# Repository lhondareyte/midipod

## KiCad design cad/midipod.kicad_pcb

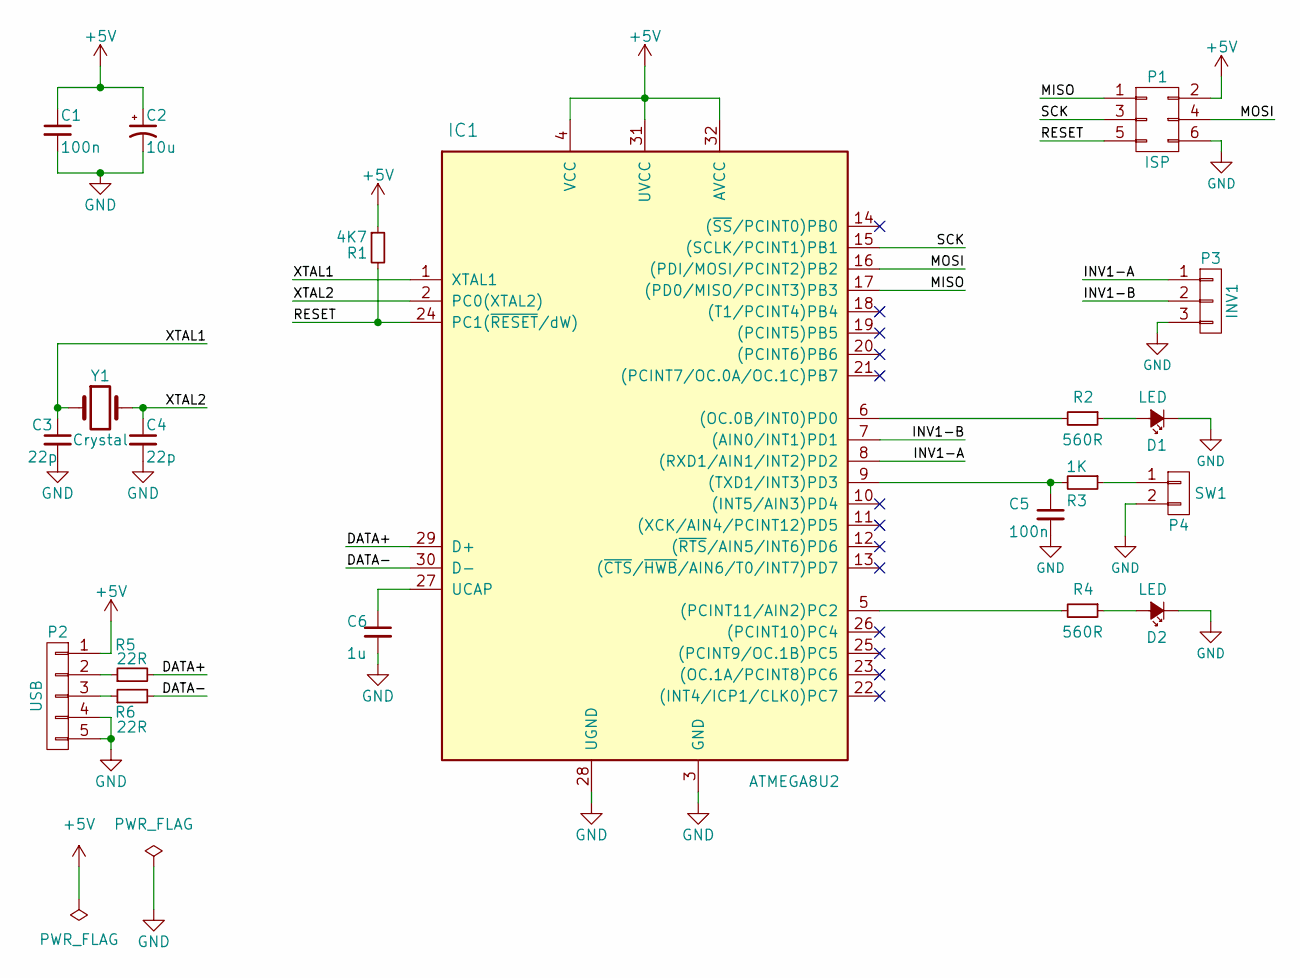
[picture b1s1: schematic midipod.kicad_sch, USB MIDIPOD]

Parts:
C1, C5: 100n; C_1206_HandSoldering
C2: 10u; C_Radial_D5_L11_P2.5
C3, C4: 22p; C_1206_HandSoldering
C6: 1u; C_1206_HandSoldering
D1, D2: LED; LED_D3.0mm_Horizontal_O1.27mm_Z2.0mm_Clear
IC1: ATMEGA8U2; TQFP-32_7x7mm_Pitch0.8mm
P1: ISP; Pin_Header_Straight_2x03
P2: USB; USB_B
P3: INV1; Pin_Header_Angled_1x03
P4: SW1; Pin_Header_Angled_1x02
R1: 4K7; R_1206_HandSoldering
R2, R4: 560R; R_1206_HandSoldering
R3: 1K; R_1206_HandSoldering
R5, R6: 22R; R_1206_HandSoldering
Y1: Crystal; Crystal_HC49-U_Vertical

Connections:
+5V: C1.1, C2.1, IC1.4 (VCC), IC1.31 (UVCC), IC1.32 (AVCC), P1.2, P2.1, R1.1
/DATA+: IC1.29 (D+), R5.2
/DATA-: IC1.30 (D-), R6.2
/INV1-A: IC1.8 ((RXD1/AIN1/INT2)PD2), P3.1
/INV1-B: IC1.7 ((AIN0/INT1)PD1), P3.2
/MISO: IC1.17 ((PD0/MISO/PCINT3)PB3), P1.1
/MOSI: IC1.16 ((PDI/MOSI/PCINT2)PB2), P1.4
/RESET: IC1.24 (PC1(~RESET/dW)), P1.5, R1.2
/SCK: IC1.15 ((SCLK/PCINT1)PB1), P1.3
/XTAL1: C3.1, IC1.1 (XTAL1), Y1.1
/XTAL2: C4.1, IC1.2 (PC0(XTAL2)), Y1.2
GND: C1.2, C2.2, C3.2, C4.2, C5.2, C6.2, D1.1 (K), D2.1 (K), IC1.3 (GND), IC1.28 (UGND), P1.6, P2.4, P2.5, P3.3, P4.2
unnamed: D1.2 (A), R2.1
unnamed: D2.2 (A), R4.1
unnamed: IC1.6 ((OC.0B/INT0)PD0), R2.2
unnamed: IC1.5 ((PCINT11/AIN2)PC2), R4.2
unnamed: C5.1, IC1.9 ((TXD1/INT3)PD3), R3.2
unnamed: C6.1, IC1.27 (UCAP)
unnamed: P2.2, R5.1
unnamed: P2.3, R6.1
unnamed: P4.1, R3.1

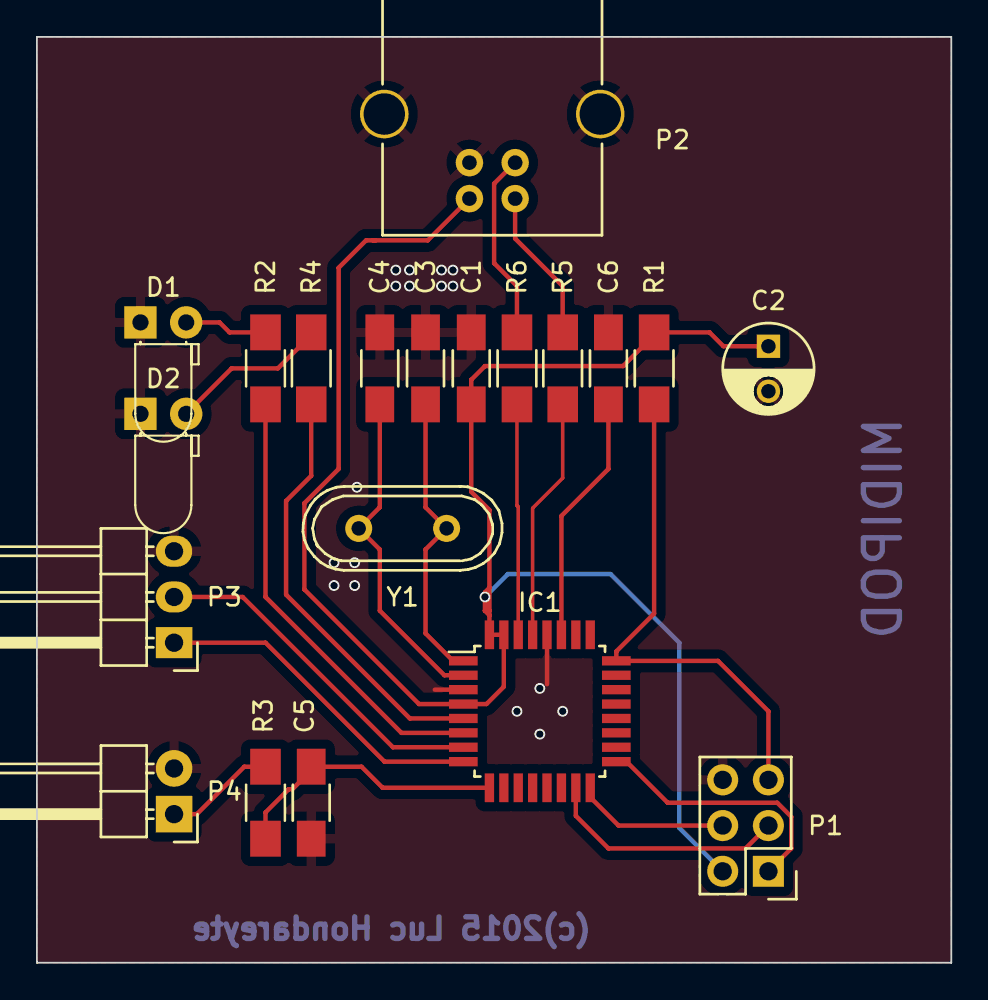
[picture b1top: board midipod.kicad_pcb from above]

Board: 2 copper layers, 50.8 x 51.4 mm, 20 parts (0 on the bottom side), 21 nets.

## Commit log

2014-03-11 Switch MIDI-USB. Premiere version fonctionnelle. Envoi d'un note unique non configurable.
2014-06-22 Switch d'offset OK. Modification PID et VID. Utilisattion des 2 Leds OK. Modification des IO conformement au schema V1.1.
2014-06-23 Ajout tempo dans la fonction SetupHardware -> Evite les erreurs USB_ERR_STALLED sous FreeBSD.
2014-08-03 Envoi d'un CC2 après le note-on. Modification de la fonction du switch 3 pos: il permet de modifier le niveau du CC2.
2018-11-19 Adding CAD and Medias files.
2018-11-19 Avoid F_CPU warning
2018-11-19 Turn on USB LED when connected
2018-11-19 Add .gitignore
2019-06-29 Add LUFA Library as a submodule.
2020-05-19 move old cad files to historic/
2020-05-19 Check electric rules passed.
2020-06-21 Adding USB connector 3D model
2021-12-23 Add .gitattributes
2022-01-15 Update to KiCad 6
2024-06-11 UPdate to KiCad 8
2025-07-26 Update to LUFA-210130
2025-09-21 Update to KiCad 9
2025-09-21 indentation

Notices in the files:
cad/midipod.kicad_pcb:
(c)2015 Luc Hondareyte
